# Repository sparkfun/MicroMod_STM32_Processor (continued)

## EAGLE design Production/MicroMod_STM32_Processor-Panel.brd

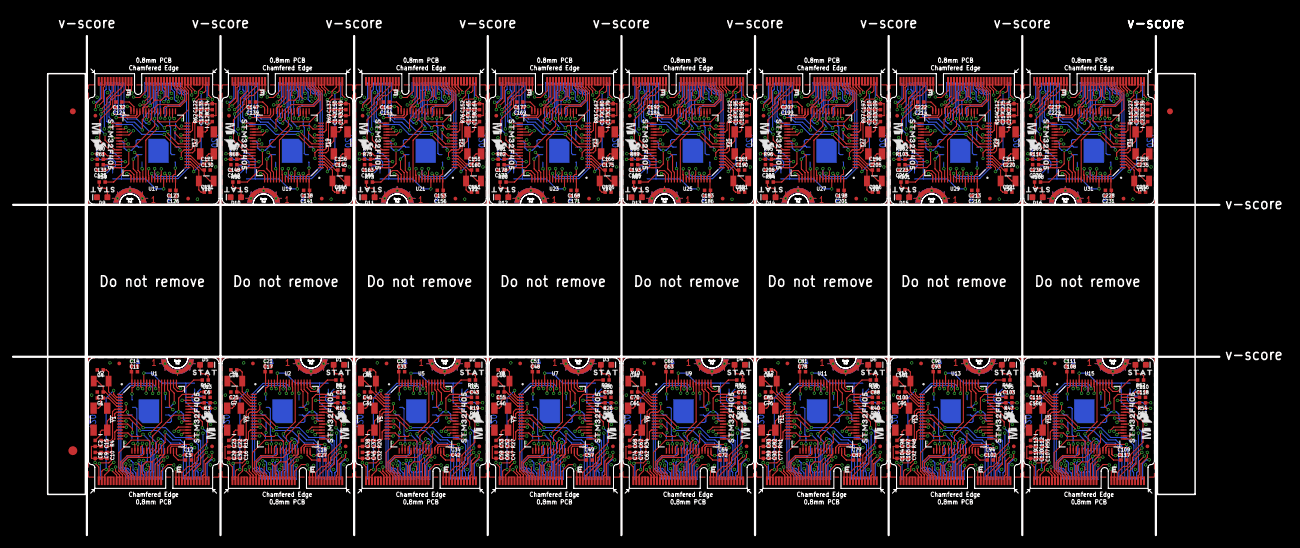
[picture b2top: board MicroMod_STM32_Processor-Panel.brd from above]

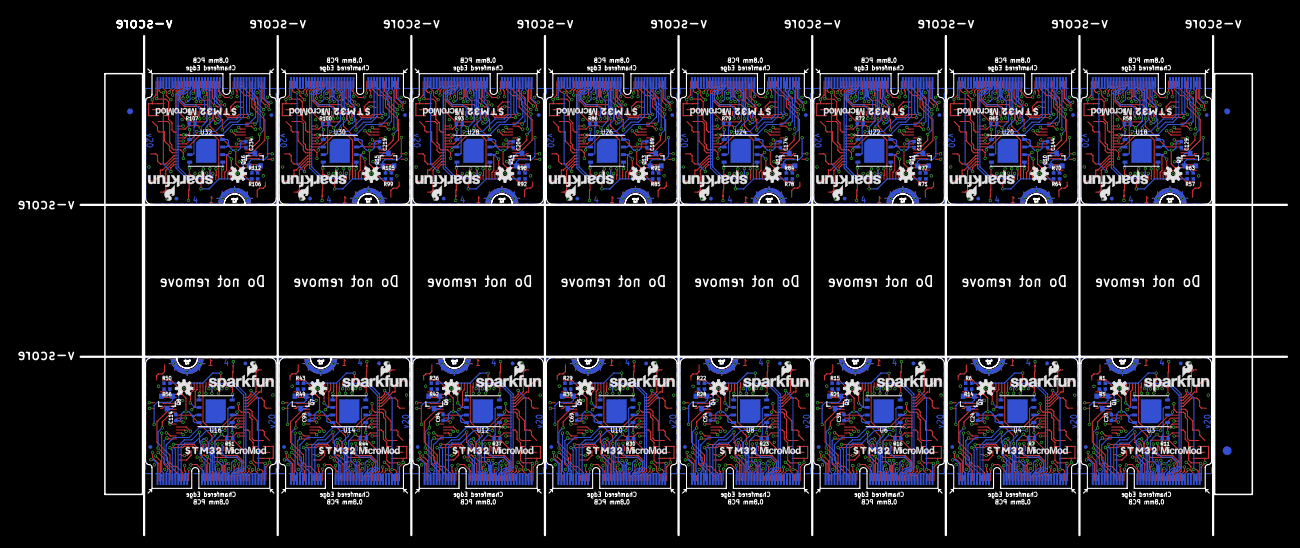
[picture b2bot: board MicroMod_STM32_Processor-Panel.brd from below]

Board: 4 copper layers, 203.2 x 84.1 mm, 662 parts (195 on the bottom side), 928 nets.

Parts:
C1, C2, C7, C23, C31, C38, C46, C53, C61, C68, C76, C83, C91, C98, C106, C113, C121, C128, C136, C143, C151, C158, C166, C173, C181, C188, C196, C203, C211, C218, C226, C233: 22pF; 0402-TIGHT
C3, C4, C25, C26, C40, C41, C55, C56, C70, C71, C85, C86, C100, C101, C115, C116, C130, C131, C145, C146, C160, C161, C175, C176, C190, C191, C205, C206, C220, C221, C235, C236: 15pF; 0402-TIGHT
C5, C6, C27, C28, C42, C43, C57, C58, C72, C73, C87, C88, C102, C103, C117, C118, C132, C133, C147, C148, C162, C163, C177, C178, C192, C193, C207, C208, C222, C223, C237, C238: 2.2uF; 0402-TIGHT
C8, C11, C12, C13, C14, C15, C17, C18, C19, C20, C21, C22, C24, C29, C33, C34, C35, C36, C37, C39, C44, C48, C49, C50, C51, C52, C54, C59, C63, C64, C65, C66, C67, C69, C74, C78, C79, C80, C81, C82, C84, C89, C93, C94, C95, C96, C97, C99, C104, C108, C109, C110, C111, C112, C114, C119, C123, C124, C125, C126, C127, C129, C134, C138, C139, C140, C141, C142, C144, C149, C153, C154, C155, C156, C157, C159, C164, C168, C169, C170, C171, C172, C174, C179, C183, C184, C185, C186, C187, C189, C194, C198, C199, C200, C201, C202, C204, C209, C213, C214, C215, C216, C217, C219, C224, C228, C229, C230, C231, C232, C234, C239: 0.1uF; 0402-TIGHT
C9, C30, C45, C60, C75, C90, C105, C120, C135, C150, C165, C180, C195, C210, C225, C240: 1.0uF; 0402-TIGHT
C10, C16, C32, C47, C62, C77, C92, C107, C122, C137, C152, C167, C182, C197, C212, C227: 4.7uF; 0402-TIGHT
D1, D2, D3, D4, D5, D6, D7, D8, D9, D10, D11, D12, D13, D14, D15, D16: BLUE; LED-0603
E$1, E$2, E$3, E$4: FIDUCIAL-1X2
E$5, E$6: FIDUCIAL-1.5X3
FD1, FD2, FD3, FD4, FD5, FD6, FD7, FD8, FD9, FD10, FD11, FD12, FD13, FD14, FD15, FD16, FD17, FD18, FD19, FD20, FD21, FD22, FD23, FD24, FD25, FD26, FD27, FD28, FD29, FD30, FD31, FD32, FD33, FD34, FD35, FD36, FD37, FD38, FD39, FD40, FD41, FD42, FD43, FD44, FD45, FD46, FD47, FD48, FD49, FD50, FD51, FD52, FD53, FD54, FD55, FD56, FD57, FD58, FD59, FD60, FD61, FD62, FD63, FD64: FIDUCIALUFIDUCIAL; FIDUCIAL-MICRO
J1, J2, J3, J4, J5, J6, J7, J8, J9, J10, J11, J12, J13, J14, J15, J16: MICROMOD-2222; M.2-CARD-E-22
LOGO1, LOGO2, LOGO5, LOGO7, LOGO9, LOGO11, LOGO13, LOGO15, LOGO17, LOGO19, LOGO21, LOGO23, LOGO25, LOGO27, LOGO29, LOGO31: OSHW-LOGOS; OSHW-LOGO-S
LOGO3, LOGO4, LOGO6, LOGO8, LOGO10, LOGO12, LOGO14, LOGO16, LOGO18, LOGO20, LOGO22, LOGO24, LOGO26, LOGO28, LOGO30, LOGO32: SFE_LOGO_NAME_FLAME.1_INCH; SFE_LOGO_NAME_FLAME_.1
Q1, Q2, Q3, Q4, Q5, Q6, Q7, Q8, Q9, Q10, Q11, Q12, Q13, Q14, Q15, Q16: SOT23-3
R1, R5, R6, R7, R11, R14, R15, R16, R21, R22, R23, R28, R29, R30, R35, R36, R37, R42, R43, R44, R49, R50, R51, R56, R57, R58, R63, R64, R65, R70, R71, R72, R77, R78, R79, R84, R85, R86, R91, R92, R93, R98, R99, R100, R105, R106, R107, R112: 100k; 0402-TIGHT
R2, R3, R9, R10, R18, R19, R25, R26, R32, R33, R39, R40, R46, R47, R53, R54, R60, R61, R67, R68, R74, R75, R81, R82, R88, R89, R95, R96, R102, R103, R109, R110: 22; 0402-TIGHT
R4, R13, R20, R27, R34, R41, R48, R55, R62, R69, R76, R83, R90, R97, R104, R111: 5.1k; 0402-TIGHT
R8, R12, R17, R24, R31, R38, R45, R52, R59, R66, R73, R80, R87, R94, R101, R108: 1k; 0402-TIGHT
U1, U2, U5, U7, U9, U11, U13, U15, U17, U19, U21, U23, U25, U27, U29, U31: STM32F405RGT6; TQFP64
U3, U4, U6, U8, U10, U12, U14, U16, U18, U20, U22, U24, U26, U28, U30, U32: W25QXX128MBIT-6X5; WSON-8-6X5
U$1, U$7, U$13, U$19, U$25, U$31, U$37, U$43, U$49, U$55, U$61, U$67, U$73, U$79, U$85, U$91: STAT0
U$2, U$8, U$14, U$20, U$26, U$32, U$38, U$44, U$50, U$56, U$62, U$68, U$74, U$80, U$86, U$92: STM320
U$3, U$9, U$15, U$21, U$27, U$33, U$39, U$45, U$51, U$57, U$63, U$69, U$75, U$81, U$87, U$93: MICROMOD_MI_LOGO_.35
U$4, U$10, U$16, U$22, U$28, U$34, U$40, U$46, U$52, U$58, U$64, U$70, U$76, U$82, U$88, U$94: STM32F4050
U$5, U$11, U$17, U$23, U$29, U$35, U$41, U$47, U$53, U$59, U$65, U$71, U$77, U$83, U$89, U$95: MICROMOD_LOGO_.3
U$6, U$12, U$18, U$24, U$30, U$36, U$42, U$48, U$54, U$60, U$66, U$72, U$78, U$84, U$90, U$96: SFE_LOGO_FLAME_.1
Y1, Y3, Y5, Y7, Y9, Y11, Y13, Y15, Y17, Y19, Y21, Y23, Y25, Y27, Y29, Y31: 12MHz; CRYSTAL-SMD-5X3.2-4PAD
Y2, Y4, Y6, Y8, Y10, Y12, Y14, Y16, Y18, Y20, Y22, Y24, Y26, Y28, Y30, Y32: 32.768kHz; CRYSTAL-SMD-3.2X1.5MM

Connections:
3.3V: C8.1, C9.1, C10.1, C11.1, C12.1, C13.1, C14.1, C20.1, J1.2, J1.74, Q1.2, R4.2, R5.2, R11.2, U1.13, U1.19, U1.32, U1.48, U1.64, U3.3, U3.7, U3.8
3.3V1: C16.1, C17.1, C18.1, C19.1, C21.1, C24.1, C29.1, C30.1, J2.2, J2.74, Q2.2, R7.2, R13.2, R14.2, U2.13, U2.19, U2.32, U2.48, U2.64, U4.3, U4.7, U4.8
3.3V2: C32.1, C33.1, C34.1, C35.1, C36.1, C39.1, C44.1, C45.1, J3.2, J3.74, Q3.2, R16.2, R20.2, R21.2, U5.13, U5.19, U5.32, U5.48, U5.64, U6.3, U6.7, U6.8
3.3V3: C47.1, C48.1, C49.1, C50.1, C51.1, C54.1, C59.1, C60.1, J4.2, J4.74, Q4.2, R23.2, R27.2, R28.2, U7.13, U7.19, U7.32, U7.48, U7.64, U8.3, U8.7, U8.8
3.3V4: C62.1, C63.1, C64.1, C65.1, C66.1, C69.1, C74.1, C75.1, J5.2, J5.74, Q5.2, R30.2, R34.2, R35.2, U9.13, U9.19, U9.32, U9.48, U9.64, U10.3, U10.7, U10.8
3.3V5: C77.1, C78.1, C79.1, C80.1, C81.1, C84.1, C89.1, C90.1, J6.2, J6.74, Q6.2, R37.2, R41.2, R42.2, U11.13, U11.19, U11.32, U11.48, U11.64, U12.3, U12.7, U12.8
3.3V6: C92.1, C93.1, C94.1, C95.1, C96.1, C99.1, C104.1, C105.1, J7.2, J7.74, Q7.2, R44.2, R48.2, R49.2, U13.13, U13.19, U13.32, U13.48, U13.64, U14.3, U14.7, U14.8
3.3V7: C107.1, C108.1, C109.1, C110.1, C111.1, C114.1, C119.1, C120.1, J8.2, J8.74, Q8.2, R51.2, R55.2, R56.2, U15.13, U15.19, U15.32, U15.48, U15.64, U16.3, U16.7, U16.8
3.3V8: C122.1, C123.1, C124.1, C125.1, C126.1, C129.1, C134.1, C135.1, J9.2, J9.74, Q9.2, R58.2, R62.2, R63.2, U17.13, U17.19, U17.32, U17.48, U17.64, U18.3, U18.7, U18.8
3.3V9: C137.1, C138.1, C139.1, C140.1, C141.1, C144.1, C149.1, C150.1, J10.2, J10.74, Q10.2, R65.2, R69.2, R70.2, U19.13, U19.19, U19.32, U19.48, U19.64, U20.3, U20.7, U20.8
3.3V10: C152.1, C153.1, C154.1, C155.1, C156.1, C159.1, C164.1, C165.1, J11.2, J11.74, Q11.2, R72.2, R76.2, R77.2, U21.13, U21.19, U21.32, U21.48, U21.64, U22.3, U22.7, U22.8
3.3V11: C167.1, C168.1, C169.1, C170.1, C171.1, C174.1, C179.1, C180.1, J12.2, J12.74, Q12.2, R79.2, R83.2, R84.2, U23.13, U23.19, U23.32, U23.48, U23.64, U24.3, U24.7, U24.8
3.3V12: C182.1, C183.1, C184.1, C185.1, C186.1, C189.1, C194.1, C195.1, J13.2, J13.74, Q13.2, R86.2, R90.2, R91.2, U25.13, U25.19, U25.32, U25.48, U25.64, U26.3, U26.7, U26.8
3.3V13: C197.1, C198.1, C199.1, C200.1, C201.1, C204.1, C209.1, C210.1, J14.2, J14.74, Q14.2, R93.2, R97.2, R98.2, U27.13, U27.19, U27.32, U27.48, U27.64, U28.3, U28.7, U28.8
3.3V14: C212.1, C213.1, C214.1, C215.1, C216.1, C219.1, C224.1, C225.1, J15.2, J15.74, Q15.2, R100.2, R104.2, R105.2, U29.13, U29.19, U29.32, U29.48, U29.64, U30.3, U30.7, U30.8
3.3V15: C227.1, C228.1, C229.1, C230.1, C231.1, C234.1, C239.1, C240.1, J16.2, J16.74, Q16.2, R107.2, R111.2, R112.2, U31.13, U31.19, U31.32, U31.48, U31.64, U32.3, U32.7, U32.8
!BOOT: J1.11, Q1.1, R5.1
!BOOT1: J2.11, Q2.1, R14.1
!BOOT2: J3.11, Q3.1, R21.1
!BOOT3: J4.11, Q4.1, R28.1
!BOOT4: J5.11, Q5.1, R35.1
!BOOT5: J6.11, Q6.1, R42.1
!BOOT6: J7.11, Q7.1, R49.1
!BOOT7: J8.11, Q8.1, R56.1
!BOOT8: J9.11, Q9.1, R63.1
!BOOT9: J10.11, Q10.1, R70.1
!BOOT10: J11.11, Q11.1, R77.1
!BOOT11: J12.11, Q12.1, R84.1
!BOOT12: J13.11, Q13.1, R91.1
!BOOT13: J14.11, Q14.1, R98.1
!BOOT14: J15.11, Q15.1, R105.1
!BOOT15: J16.11, Q16.1, R112.1
!CS: J1.55, U1.24
!CS1: J2.55, U2.24
!CS2: J3.55, U5.24
!CS3: J4.55, U7.24
!CS4: J5.55, U9.24
!CS5: J6.55, U11.24
!CS6: J7.55, U13.24
!CS7: J8.55, U15.24
!CS8: J9.55, U17.24
!CS9: J10.55, U19.24
!CS10: J11.55, U21.24
!CS11: J12.55, U23.24
!CS12: J13.55, U25.24
!CS13: J14.55, U27.24
!CS14: J15.55, U29.24
!CS15: J16.55, U31.24
!INT: J1.16, U1.27
!INT1: J2.16, U2.27
!INT2: J3.16, U5.27
!INT3: J4.16, U7.27
!INT4: J5.16, U9.27
!INT5: J6.16, U11.27
!INT6: J7.16, U13.27
!INT7: J8.16, U15.27
!INT8: J9.16, U17.27
!INT9: J10.16, U19.27
!INT10: J11.16, U21.27
!INT11: J12.16, U23.27
!INT12: J13.16, U25.27
!INT13: J14.16, U27.27
!INT14: J15.16, U29.27
!INT15: J16.16, U31.27
!RESET: C15.1, J1.6, R4.1, U1.7
!RESET1: C22.1, J2.6, R13.1, U2.7
!RESET2: C37.1, J3.6, R20.1, U5.7
!RESET3: C52.1, J4.6, R27.1, U7.7
!RESET4: C67.1, J5.6, R34.1, U9.7
!RESET5: C82.1, J6.6, R41.1, U11.7
!RESET6: C97.1, J7.6, R48.1, U13.7
!RESET7: C112.1, J8.6, R55.1, U15.7
!RESET8: C127.1, J9.6, R62.1, U17.7
!RESET9: C142.1, J10.6, R69.1, U19.7
!RESET10: C157.1, J11.6, R76.1, U21.7
!RESET11: C172.1, J12.6, R83.1, U23.7
!RESET12: C187.1, J13.6, R90.1, U25.7
!RESET13: C202.1, J14.6, R97.1, U27.7
!RESET14: C217.1, J15.6, R104.1, U29.7
!RESET15: C232.1, J16.6, R111.1, U31.7
A0: J1.34, U1.25
A1: J1.38, U1.26
A2: J2.34, U2.25
A3: J2.38, U2.26
A4: J3.34, U5.25
A5: J3.38, U5.26
A6: J4.34, U7.25
A7: J4.38, U7.26
A8: J5.34, U9.25
A9: J5.38, U9.26
A10: J6.34, U11.25
A11: J6.38, U11.26
A12: J7.34, U13.25
A13: J7.38, U13.26
A14: J8.34, U15.25
A15: J8.38, U15.26
A16: J9.34, U17.25
A17: J9.38, U17.26
A18: J10.34, U19.25
A19: J10.38, U19.26
A20: J11.34, U21.25
A21: J11.38, U21.26
A22: J12.34, U23.25
A23: J12.38, U23.26
A24: J13.34, U25.25
A25: J13.38, U25.26
A26: J14.34, U27.25
A27: J14.38, U27.26
A28: J15.34, U29.25
A29: J15.38, U29.26
A30: J16.34, U31.25
A31: J16.38, U31.26
AUD_BCLK: J1.50, U1.55
AUD_BCLK1: J2.50, U2.55
AUD_BCLK2: J3.50, U5.55
AUD_BCLK3: J4.50, U7.55
AUD_BCLK4: J5.50, U9.55
AUD_BCLK5: J6.50, U11.55
AUD_BCLK6: J7.50, U13.55
AUD_BCLK7: J8.50, U15.55
AUD_BCLK8: J9.50, U17.55
AUD_BCLK9: J10.50, U19.55
AUD_BCLK10: J11.50, U21.55
AUD_BCLK11: J12.50, U23.55
AUD_BCLK12: J13.50, U25.55
AUD_BCLK13: J14.50, U27.55
AUD_BCLK14: J15.50, U29.55
AUD_BCLK15: J16.50, U31.55
AUD_IN: J1.54, U1.57
AUD_IN1: J2.54, U2.57
AUD_IN2: J3.54, U5.57
AUD_IN3: J4.54, U7.57
AUD_IN4: J5.54, U9.57
AUD_IN5: J6.54, U11.57
AUD_IN6: J7.54, U13.57
AUD_IN7: J8.54, U15.57
AUD_IN8: J9.54, U17.57
AUD_IN9: J10.54, U19.57
AUD_IN10: J11.54, U21.57
AUD_IN11: J12.54, U23.57
AUD_IN12: J13.54, U25.57
AUD_IN13: J14.54, U27.57
AUD_IN14: J15.54, U29.57
AUD_IN15: J16.54, U31.57
AUD_LRCLK: J1.52, U1.20
AUD_LRCLK1: J2.52, U2.20
AUD_LRCLK2: J3.52, U5.20
AUD_LRCLK3: J4.52, U7.20
AUD_LRCLK4: J5.52, U9.20
AUD_LRCLK5: J6.52, U11.20
AUD_LRCLK6: J7.52, U13.20
AUD_LRCLK7: J8.52, U15.20
AUD_LRCLK8: J9.52, U17.20
AUD_LRCLK9: J10.52, U19.20
AUD_LRCLK10: J11.52, U21.20
AUD_LRCLK11: J12.52, U23.20
AUD_LRCLK12: J13.52, U25.20
AUD_LRCLK13: J14.52, U27.20
AUD_LRCLK14: J15.52, U29.20
AUD_LRCLK15: J16.52, U31.20
AUD_OUT: J1.56, U1.56
AUD_OUT1: J2.56, U2.56
AUD_OUT2: J3.56, U5.56
AUD_OUT3: J4.56, U7.56
AUD_OUT4: J5.56, U9.56
AUD_OUT5: J6.56, U11.56
AUD_OUT6: J7.56, U13.56
AUD_OUT7: J8.56, U15.56
AUD_OUT8: J9.56, U17.56
AUD_OUT9: J10.56, U19.56
AUD_OUT10: J11.56, U21.56
AUD_OUT11: J12.56, U23.56
AUD_OUT12: J13.56, U25.56
AUD_OUT13: J14.56, U27.56
AUD_OUT14: J15.56, U29.56
AUD_OUT15: J16.56, U31.56
BATT_VIN: J1.49, U1.15
BATT_VIN1: J2.49, U2.15
BATT_VIN2: J3.49, U5.15
BATT_VIN3: J4.49, U7.15
BATT_VIN4: J5.49, U9.15
BATT_VIN5: J6.49, U11.15
BATT_VIN6: J7.49, U13.15
BATT_VIN7: J8.49, U15.15
BATT_VIN8: J9.49, U17.15
BATT_VIN9: J10.49, U19.15
BATT_VIN10: J11.49, U21.15
BATT_VIN11: J12.49, U23.15
BATT_VIN12: J13.49, U25.15
BATT_VIN13: J14.49, U27.15
BATT_VIN14: J15.49, U29.15
BATT_VIN15: J16.49, U31.15
BOOT0: Q1.3, R1.2, U1.60
BOOT1: Q2.3, R6.2, U2.60
BOOT2: Q3.3, R15.2, U5.60
BOOT3: Q4.3, R22.2, U7.60
BOOT4: Q5.3, R29.2, U9.60
BOOT5: Q6.3, R36.2, U11.60
BOOT6: Q7.3, R43.2, U13.60
BOOT7: Q8.3, R50.2, U15.60
BOOT8: Q9.3, R57.2, U17.60
BOOT9: Q10.3, R64.2, U19.60
BOOT10: Q11.3, R71.2, U21.60
BOOT11: Q12.3, R78.2, U23.60
BOOT12: Q13.3, R85.2, U25.60
BOOT13: Q14.3, R92.2, U27.60
BOOT14: Q15.3, R99.2, U29.60
BOOT15: Q16.3, R106.2, U31.60
CAN_RX: J1.41, U1.61
CAN_RX1: J2.41, U2.61
CAN_RX2: J3.41, U5.61
CAN_RX3: J4.41, U7.61
CAN_RX4: J5.41, U9.61
CAN_RX5: J6.41, U11.61
CAN_RX6: J7.41, U13.61
CAN_RX7: J8.41, U15.61
CAN_RX8: J9.41, U17.61
CAN_RX9: J10.41, U19.61
CAN_RX10: J11.41, U21.61
CAN_RX11: J12.41, U23.61
CAN_RX12: J13.41, U25.61
CAN_RX13: J14.41, U27.61
CAN_RX14: J15.41, U29.61
CAN_RX15: J16.41, U31.61
CAN_TX: J1.43, U1.62
CAN_TX1: J2.43, U2.62
CAN_TX2: J3.43, U5.62
CAN_TX3: J4.43, U7.62
CAN_TX4: J5.43, U9.62
CAN_TX5: J6.43, U11.62
CAN_TX6: J7.43, U13.62
CAN_TX7: J8.43, U15.62
CAN_TX8: J9.43, U17.62
CAN_TX9: J10.43, U19.62
CAN_TX10: J11.43, U21.62
CAN_TX11: J12.43, U23.62
CAN_TX12: J13.43, U25.62
CAN_TX13: J14.43, U27.62
CAN_TX14: J15.43, U29.62
CAN_TX15: J16.43, U31.62
D0: J1.10, U1.8
D1: J1.18, U1.9
D2: J2.10, U2.8
D3: J2.18, U2.9
D4: J3.10, U5.8
D5: J3.18, U5.9
D6: J4.10, U7.8
D7: J4.18, U7.9
D8: J5.10, U9.8
D9: J5.18, U9.9
D10: J6.10, U11.8
D11: J6.18, U11.9
D12: J7.10, U13.8
D13: J7.18, U13.9
D14: J8.10, U15.8
D15: J8.18, U15.9
D16: J9.10, U17.8
D17: J9.18, U17.9
D18: J10.10, U19.8
D19: J10.18, U19.9
D20: J11.10, U21.8
D21: J11.18, U21.9
D22: J12.10, U23.8
D23: J12.18, U23.9
D24: J13.10, U25.8
D25: J13.18, U25.9
D26: J14.10, U27.8
D27: J14.18, U27.9
D28: J15.10, U29.8
D29: J15.18, U29.9
D30: J16.10, U31.8
D31: J16.18, U31.9
D+: J1.3, R3.1
D+1: J2.3, R10.1
D+2: J3.3, R19.1
D+3: J4.3, R26.1
D+4: J5.3, R33.1
D+5: J6.3, R40.1
D+6: J7.3, R47.1
D+7: J8.3, R54.1
D+8: J9.3, R61.1
D+9: J10.3, R68.1
D+10: J11.3, R75.1
D+11: J12.3, R82.1
D+12: J13.3, R89.1
D+13: J14.3, R96.1
D+14: J15.3, R103.1
D+15: J16.3, R110.1
D-: J1.5, R2.1
D-1: J2.5, R9.1
D-2: J3.5, R18.1
D-3: J4.5, R25.1
D-4: J5.5, R32.1
D-5: J6.5, R39.1
D-6: J7.5, R46.1
D-7: J8.5, R53.1
D-8: J9.5, R60.1
D-9: J10.5, R67.1
D-10: J11.5, R74.1
D-11: J12.5, R81.1
D-12: J13.5, R88.1
D-13: J14.5, R95.1
D-14: J15.5, R102.1
D-15: J16.5, R109.1
FLASH_!CS: R11.1, U1.11, U3.1
FLASH_!CS1: R7.1, U2.11, U4.1
FLASH_!CS2: R16.1, U5.11, U6.1
FLASH_!CS3: R23.1, U7.11, U8.1
FLASH_!CS4: R30.1, U9.11, U10.1
FLASH_!CS5: R37.1, U11.11, U12.1
FLASH_!CS6: R44.1, U13.11, U14.1
FLASH_!CS7: R51.1, U15.11, U16.1
FLASH_!CS8: R58.1, U17.11, U18.1
FLASH_!CS9: R65.1, U19.11, U20.1
FLASH_!CS10: R72.1, U21.11, U22.1
FLASH_!CS11: R79.1, U23.11, U24.1
FLASH_!CS12: R86.1, U25.11, U26.1
FLASH_!CS13: R93.1, U27.11, U28.1
FLASH_!CS14: R100.1, U29.11, U30.1
FLASH_!CS15: R107.1, U31.11, U32.1
FLASH_SCK: U1.51, U3.6
FLASH_SCK1: U2.51, U4.6
FLASH_SCK2: U5.51, U6.6
FLASH_SCK3: U7.51, U8.6
FLASH_SCK4: U9.51, U10.6
FLASH_SCK5: U11.51, U12.6
FLASH_SCK6: U13.51, U14.6
FLASH_SCK7: U15.51, U16.6
FLASH_SCK8: U17.51, U18.6
FLASH_SCK9: U19.51, U20.6
FLASH_SCK10: U21.51, U22.6
FLASH_SCK11: U23.51, U24.6
FLASH_SCK12: U25.51, U26.6
FLASH_SCK13: U27.51, U28.6
FLASH_SCK14: U29.51, U30.6
FLASH_SCK15: U31.51, U32.6
FLASH_SDI: U1.53, U3.5
FLASH_SDI1: U2.53, U4.5
FLASH_SDI2: U5.53, U6.5
FLASH_SDI3: U7.53, U8.5
FLASH_SDI4: U9.53, U10.5
FLASH_SDI5: U11.53, U12.5
FLASH_SDI6: U13.53, U14.5
FLASH_SDI7: U15.53, U16.5
FLASH_SDI8: U17.53, U18.5
FLASH_SDI9: U19.53, U20.5
FLASH_SDI10: U21.53, U22.5
FLASH_SDI11: U23.53, U24.5
FLASH_SDI12: U25.53, U26.5
FLASH_SDI13: U27.53, U28.5
FLASH_SDI14: U29.53, U30.5
FLASH_SDI15: U31.53, U32.5
FLASH_SDO: U1.52, U3.2
FLASH_SDO1: U2.52, U4.2
FLASH_SDO2: U5.52, U6.2
FLASH_SDO3: U7.52, U8.2
FLASH_SDO4: U9.52, U10.2
FLASH_SDO5: U11.52, U12.2
FLASH_SDO6: U13.52, U14.2
FLASH_SDO7: U15.52, U16.2
FLASH_SDO8: U17.52, U18.2
FLASH_SDO9: U19.52, U20.2
FLASH_SDO10: U21.52, U22.2
FLASH_SDO11: U23.52, U24.2
FLASH_SDO12: U25.52, U26.2
FLASH_SDO13: U27.52, U28.2
FLASH_SDO14: U29.52, U30.2
FLASH_SDO15: U31.52, U32.2
G0: J1.40, U1.54
G1: J1.42, U1.41
G2: J1.44, U1.14
G3: J1.46, U1.39
G4: J1.48, U1.40
G5: J1.73, U1.2
G6: J1.71, U1.10
G7: J2.73, U2.2
G8: J2.71, U2.10
G9: J2.46, U2.39
G10: J2.48, U2.40
G11: J2.40, U2.54
G12: J2.42, U2.41
G13: J2.44, U2.14
G14: J3.73, U5.2
G15: J3.71, U5.10
G16: J3.46, U5.39
G17: J3.48, U5.40
G18: J3.40, U5.54
G19: J3.42, U5.41
G20: J3.44, U5.14
G21: J4.73, U7.2
G22: J4.71, U7.10
G23: J4.46, U7.39
G24: J4.48, U7.40
G25: J4.40, U7.54
G26: J4.42, U7.41
G27: J4.44, U7.14
G28: J5.73, U9.2
G29: J5.71, U9.10
G30: J5.46, U9.39
G31: J5.48, U9.40
G32: J5.40, U9.54
G33: J5.42, U9.41
G34: J5.44, U9.14
G35: J6.73, U11.2
G36: J6.71, U11.10
G37: J6.46, U11.39
G38: J6.48, U11.40
G39: J6.40, U11.54
G40: J6.42, U11.41
G41: J6.44, U11.14
G42: J7.73, U13.2
G43: J7.71, U13.10
G44: J7.46, U13.39
G45: J7.48, U13.40
G46: J7.40, U13.54
G47: J7.42, U13.41
G48: J7.44, U13.14
G49: J8.73, U15.2
G50: J8.71, U15.10
G51: J8.46, U15.39
G52: J8.48, U15.40
G53: J8.40, U15.54
G54: J8.42, U15.41
G55: J8.44, U15.14
G56: J9.73, U17.2
G57: J9.71, U17.10
G58: J9.46, U17.39
G59: J9.48, U17.40
G60: J9.40, U17.54
G61: J9.42, U17.41
G62: J9.44, U17.14
G63: J10.73, U19.2
G64: J10.71, U19.10
G65: J10.46, U19.39
G66: J10.48, U19.40
G67: J10.40, U19.54
G68: J10.42, U19.41
G69: J10.44, U19.14
G70: J11.73, U21.2
G71: J11.71, U21.10
G72: J11.46, U21.39
G73: J11.48, U21.40
G74: J11.40, U21.54
G75: J11.42, U21.41
G76: J11.44, U21.14
G77: J12.73, U23.2
G78: J12.71, U23.10
G79: J12.46, U23.39
G80: J12.48, U23.40
G81: J12.40, U23.54
G82: J12.42, U23.41
G83: J12.44, U23.14
G84: J13.73, U25.2
G85: J13.71, U25.10
G86: J13.46, U25.39
G87: J13.48, U25.40
G88: J13.40, U25.54
G89: J13.42, U25.41
G90: J13.44, U25.14
G91: J14.73, U27.2
G92: J14.71, U27.10
G93: J14.46, U27.39
G94: J14.48, U27.40
G95: J14.40, U27.54
G96: J14.42, U27.41
G97: J14.44, U27.14
G98: J15.73, U29.2
G99: J15.71, U29.10
G100: J15.46, U29.39
G101: J15.48, U29.40
G102: J15.40, U29.54
G103: J15.42, U29.41
G104: J15.44, U29.14
G105: J16.73, U31.2
G106: J16.71, U31.10
G107: J16.46, U31.39
G108: J16.48, U31.40
G109: J16.40, U31.54
G110: J16.42, U31.41
G111: J16.44, U31.14
GND: C1.2, C2.2, C3.2, C4.2, C5.2, C6.2, C8.2, C9.2, C10.2, C11.2, C12.2, C13.2, C14.2, C15.2, C20.2, D5.C, J1.1, J1.7, J1.33, J1.36, J1.39, J1.45, J1.75, J1.GND1, J1.GND2, J1.GND3, R1.1, U1.12, U1.16, U1.17, U1.18, U1.28, U1.63, U3.4
GND1: C7.2, C16.2, C17.2, C18.2, C19.2, C21.2, C22.2, C23.2, C24.2, C25.2, C26.2, C27.2, C28.2, C29.2, C30.2, D1.C, J2.1, J2.7, J2.33, J2.36, J2.39, J2.45, J2.75, J2.GND1, J2.GND2, J2.GND3, R6.1, U2.12, U2.16, U2.17, U2.18, U2.28, U2.63, U4.4
GND2: C31.2, C32.2, C33.2, C34.2, C35.2, C36.2, C37.2, C38.2, C39.2, C40.2, C41.2, C42.2, C43.2, C44.2, C45.2, D2.C, J3.1, J3.7, J3.33, J3.36, J3.39, J3.45, J3.75, J3.GND1, J3.GND2, J3.GND3, R15.1, U5.12, U5.16, U5.17, U5.18, U5.28, U5.63, U6.4
GND3: C46.2, C47.2, C48.2, C49.2, C50.2, C51.2, C52.2, C53.2, C54.2, C55.2, C56.2, C57.2, C58.2, C59.2, C60.2, D3.C, J4.1, J4.7, J4.33, J4.36, J4.39, J4.45, J4.75, J4.GND1, J4.GND2, J4.GND3, R22.1, U7.12, U7.16, U7.17, U7.18, U7.28, U7.63, U8.4
GND4: C61.2, C62.2, C63.2, C64.2, C65.2, C66.2, C67.2, C68.2, C69.2, C70.2, C71.2, C72.2, C73.2, C74.2, C75.2, D4.C, J5.1, J5.7, J5.33, J5.36, J5.39, J5.45, J5.75, J5.GND1, J5.GND2, J5.GND3, R29.1, U9.12, U9.16, U9.17, U9.18, U9.28, U9.63, U10.4
GND5: C76.2, C77.2, C78.2, C79.2, C80.2, C81.2, C82.2, C83.2, C84.2, C85.2, C86.2, C87.2, C88.2, C89.2, C90.2, D6.C, J6.1, J6.7, J6.33, J6.36, J6.39, J6.45, J6.75, J6.GND1, J6.GND2, J6.GND3, R36.1, U11.12, U11.16, U11.17, U11.18, U11.28, U11.63, U12.4
GND6: C91.2, C92.2, C93.2, C94.2, C95.2, C96.2, C97.2, C98.2, C99.2, C100.2, C101.2, C102.2, C103.2, C104.2, C105.2, D7.C, J7.1, J7.7, J7.33, J7.36, J7.39, J7.45, J7.75, J7.GND1, J7.GND2, J7.GND3, R43.1, U13.12, U13.16, U13.17, U13.18, U13.28, U13.63, U14.4
GND7: C106.2, C107.2, C108.2, C109.2, C110.2, C111.2, C112.2, C113.2, C114.2, C115.2, C116.2, C117.2, C118.2, C119.2, C120.2, D8.C, J8.1, J8.7, J8.33, J8.36, J8.39, J8.45, J8.75, J8.GND1, J8.GND2, J8.GND3, R50.1, U15.12, U15.16, U15.17, U15.18, U15.28, U15.63, U16.4
GND8: C121.2, C122.2, C123.2, C124.2, C125.2, C126.2, C127.2, C128.2, C129.2, C130.2, C131.2, C132.2, C133.2, C134.2, C135.2, D9.C, J9.1, J9.7, J9.33, J9.36, J9.39, J9.45, J9.75, J9.GND1, J9.GND2, J9.GND3, R57.1, U17.12, U17.16, U17.17, U17.18, U17.28, U17.63, U18.4
GND9: C136.2, C137.2, C138.2, C139.2, C140.2, C141.2, C142.2, C143.2, C144.2, C145.2, C146.2, C147.2, C148.2, C149.2, C150.2, D10.C, J10.1, J10.7, J10.33, J10.36, J10.39, J10.45, J10.75, J10.GND1, J10.GND2, J10.GND3, R64.1, U19.12, U19.16, U19.17, U19.18, U19.28, U19.63, U20.4
GND10: C151.2, C152.2, C153.2, C154.2, C155.2, C156.2, C157.2, C158.2, C159.2, C160.2, C161.2, C162.2, C163.2, C164.2, C165.2, D11.C, J11.1, J11.7, J11.33, J11.36, J11.39, J11.45, J11.75, J11.GND1, J11.GND2, J11.GND3, R71.1, U21.12, U21.16, U21.17, U21.18, U21.28, U21.63, U22.4
GND11: C166.2, C167.2, C168.2, C169.2, C170.2, C171.2, C172.2, C173.2, C174.2, C175.2, C176.2, C177.2, C178.2, C179.2, C180.2, D12.C, J12.1, J12.7, J12.33, J12.36, J12.39, J12.45, J12.75, J12.GND1, J12.GND2, J12.GND3, R78.1, U23.12, U23.16, U23.17, U23.18, U23.28, U23.63, U24.4
GND12: C181.2, C182.2, C183.2, C184.2, C185.2, C186.2, C187.2, C188.2, C189.2, C190.2, C191.2, C192.2, C193.2, C194.2, C195.2, D13.C, J13.1, J13.7, J13.33, J13.36, J13.39, J13.45, J13.75, J13.GND1, J13.GND2, J13.GND3, R85.1, U25.12, U25.16, U25.17, U25.18, U25.28, U25.63, U26.4
GND13: C196.2, C197.2, C198.2, C199.2, C200.2, C201.2, C202.2, C203.2, C204.2, C205.2, C206.2, C207.2, C208.2, C209.2, C210.2, D14.C, J14.1, J14.7, J14.33, J14.36, J14.39, J14.45, J14.75, J14.GND1, J14.GND2, J14.GND3, R92.1, U27.12, U27.16, U27.17, U27.18, U27.28, U27.63, U28.4
GND14: C211.2, C212.2, C213.2, C214.2, C215.2, C216.2, C217.2, C218.2, C219.2, C220.2, C221.2, C222.2, C223.2, C224.2, C225.2, D15.C, J15.1, J15.7, J15.33, J15.36, J15.39, J15.45, J15.75, J15.GND1, J15.GND2, J15.GND3, R99.1, U29.12, U29.16, U29.17, U29.18, U29.28, U29.63, U30.4
GND15: C226.2, C227.2, C228.2, C229.2, C230.2, C231.2, C232.2, C233.2, C234.2, C235.2, C236.2, C237.2, C238.2, C239.2, C240.2, D16.C, J16.1, J16.7, J16.33, J16.36, J16.39, J16.45, J16.75, J16.GND1, J16.GND2, J16.GND3, R106.1, U31.12, U31.16, U31.17, U31.18, U31.28, U31.63, U32.4
HOST_D+: J1.35, U1.36
HOST_D+1: J2.35, U2.36
HOST_D+2: J3.35, U5.36
HOST_D+3: J4.35, U7.36
HOST_D+4: J5.35, U9.36
HOST_D+5: J6.35, U11.36
HOST_D+6: J7.35, U13.36
HOST_D+7: J8.35, U15.36
HOST_D+8: J9.35, U17.36
HOST_D+9: J10.35, U19.36
HOST_D+10: J11.35, U21.36
HOST_D+11: J12.35, U23.36
HOST_D+12: J13.35, U25.36
HOST_D+13: J14.35, U27.36
HOST_D+14: J15.35, U29.36
HOST_D+15: J16.35, U31.36
HOST_D-: J1.37, U1.35
HOST_D-1: J2.37, U2.35
HOST_D-2: J3.37, U5.35
HOST_D-3: J4.37, U7.35
HOST_D-4: J5.37, U9.35
HOST_D-5: J6.37, U11.35
HOST_D-6: J7.37, U13.35
HOST_D-7: J8.37, U15.35
HOST_D-8: J9.37, U17.35
HOST_D-9: J10.37, U19.35
HOST_D-10: J11.37, U21.35
HOST_D-11: J12.37, U23.35
HOST_D-12: J13.37, U25.35
HOST_D-13: J14.37, U27.35
HOST_D-14: J15.37, U29.35
HOST_D-15: J16.37, U31.35
HOST_ID: J1.8, U1.33
HOST_ID1: J2.8, U2.33
HOST_ID2: J3.8, U5.33
HOST_ID3: J4.8, U7.33
HOST_ID4: J5.8, U9.33
HOST_ID5: J6.8, U11.33
HOST_ID6: J7.8, U13.33
HOST_ID7: J8.8, U15.33
HOST_ID8: J9.8, U17.33
HOST_ID9: J10.8, U19.33
HOST_ID10: J11.8, U21.33
HOST_ID11: J12.8, U23.33
HOST_ID12: J13.8, U25.33
HOST_ID13: J14.8, U27.33
HOST_ID14: J15.8, U29.33
HOST_ID15: J16.8, U31.33
HOST_VBUS: J1.63, U1.34
HOST_VBUS1: J2.63, U2.34
HOST_VBUS2: J3.63, U5.34
HOST_VBUS3: J4.63, U7.34
HOST_VBUS4: J5.63, U9.34
HOST_VBUS5: J6.63, U11.34
HOST_VBUS6: J7.63, U13.34
HOST_VBUS7: J8.63, U15.34
HOST_VBUS8: J9.63, U17.34
HOST_VBUS9: J10.63, U19.34
HOST_VBUS10: J11.63, U21.34
HOST_VBUS11: J12.63, U23.34
HOST_VBUS12: J13.63, U25.34
HOST_VBUS13: J14.63, U27.34
HOST_VBUS14: J15.63, U29.34
HOST_VBUS15: J16.63, U31.34
unnamed: D5.A, R12.1
unnamed: R2.2, U1.44
unnamed: R3.2, U1.45
unnamed: C26.1, U2.3, Y4.P$2
unnamed: C4.1, U1.3, Y2.P$2
unnamed: C3.1, U1.4, Y2.P$1
unnamed: C2.1, U1.6, Y1.3
unnamed: C1.1, U1.5, Y1.1
unnamed: C25.1, U2.4, Y4.P$1
unnamed: C23.1, U2.6, Y3.3
unnamed: C7.1, U2.5, Y3.1
unnamed: C28.1, U2.47
unnamed: C27.1, U2.31
unnamed: D1.A, R8.1
unnamed: R9.2, U2.44
unnamed: R10.2, U2.45
unnamed: C41.1, U5.3, Y6.P$2
unnamed: C40.1, U5.4, Y6.P$1
unnamed: C38.1, U5.6, Y5.3
unnamed: C31.1, U5.5, Y5.1
unnamed: C43.1, U5.47
unnamed: C42.1, U5.31
unnamed: D2.A, R17.1
unnamed: R18.2, U5.44
unnamed: R19.2, U5.45
unnamed: C56.1, U7.3, Y8.P$2
unnamed: C55.1, U7.4, Y8.P$1
unnamed: C53.1, U7.6, Y7.3
unnamed: C46.1, U7.5, Y7.1
unnamed: C58.1, U7.47
unnamed: C57.1, U7.31
unnamed: D3.A, R24.1
unnamed: R25.2, U7.44
unnamed: R26.2, U7.45
unnamed: C71.1, U9.3, Y10.P$2
unnamed: C70.1, U9.4, Y10.P$1
unnamed: C68.1, U9.6, Y9.3
unnamed: C61.1, U9.5, Y9.1
unnamed: C73.1, U9.47
unnamed: C72.1, U9.31
unnamed: D4.A, R31.1
unnamed: R32.2, U9.44
unnamed: R33.2, U9.45
unnamed: C86.1, U11.3, Y12.P$2
unnamed: C6.1, U1.47
unnamed: C5.1, U1.31
unnamed: C85.1, U11.4, Y12.P$1
unnamed: C83.1, U11.6, Y11.3
unnamed: C76.1, U11.5, Y11.1
unnamed: C88.1, U11.47
unnamed: C87.1, U11.31
unnamed: D6.A, R38.1
unnamed: R39.2, U11.44
unnamed: R40.2, U11.45
unnamed: C101.1, U13.3, Y14.P$2
unnamed: C100.1, U13.4, Y14.P$1
unnamed: C98.1, U13.6, Y13.3
unnamed: C91.1, U13.5, Y13.1
unnamed: C103.1, U13.47
unnamed: C102.1, U13.31
unnamed: D7.A, R45.1
unnamed: R46.2, U13.44
unnamed: R47.2, U13.45
unnamed: C116.1, U15.3, Y16.P$2
unnamed: C115.1, U15.4, Y16.P$1
unnamed: C113.1, U15.6, Y15.3
unnamed: C106.1, U15.5, Y15.1
unnamed: C118.1, U15.47
unnamed: C117.1, U15.31
unnamed: D8.A, R52.1
unnamed: R53.2, U15.44
unnamed: R54.2, U15.45
unnamed: C131.1, U17.3, Y18.P$2
unnamed: C130.1, U17.4, Y18.P$1
unnamed: C128.1, U17.6, Y17.3
unnamed: C121.1, U17.5, Y17.1
unnamed: C133.1, U17.47
unnamed: C132.1, U17.31
unnamed: D9.A, R59.1
unnamed: R60.2, U17.44
unnamed: R61.2, U17.45
unnamed: C146.1, U19.3, Y20.P$2
unnamed: C145.1, U19.4, Y20.P$1
unnamed: C143.1, U19.6, Y19.3
unnamed: C136.1, U19.5, Y19.1
unnamed: C148.1, U19.47
unnamed: C147.1, U19.31
unnamed: D10.A, R66.1
unnamed: R67.2, U19.44
unnamed: R68.2, U19.45
unnamed: C161.1, U21.3, Y22.P$2
unnamed: C160.1, U21.4, Y22.P$1
unnamed: C158.1, U21.6, Y21.3
unnamed: C151.1, U21.5, Y21.1
unnamed: C163.1, U21.47
unnamed: C162.1, U21.31
unnamed: D11.A, R73.1
unnamed: R74.2, U21.44
unnamed: R75.2, U21.45
unnamed: C176.1, U23.3, Y24.P$2
unnamed: C175.1, U23.4, Y24.P$1
unnamed: C173.1, U23.6, Y23.3
unnamed: C166.1, U23.5, Y23.1
unnamed: C178.1, U23.47
unnamed: C177.1, U23.31
unnamed: D12.A, R80.1
unnamed: R81.2, U23.44
unnamed: R82.2, U23.45
unnamed: C191.1, U25.3, Y26.P$2
unnamed: C190.1, U25.4, Y26.P$1
unnamed: C188.1, U25.6, Y25.3
unnamed: C181.1, U25.5, Y25.1
unnamed: C193.1, U25.47
unnamed: C192.1, U25.31
unnamed: D13.A, R87.1
unnamed: R88.2, U25.44
unnamed: R89.2, U25.45
unnamed: C206.1, U27.3, Y28.P$2
unnamed: C205.1, U27.4, Y28.P$1
unnamed: C203.1, U27.6, Y27.3
unnamed: C196.1, U27.5, Y27.1
unnamed: C208.1, U27.47
unnamed: C207.1, U27.31
unnamed: D14.A, R94.1
unnamed: R95.2, U27.44
unnamed: R96.2, U27.45
unnamed: C221.1, U29.3, Y30.P$2
unnamed: C220.1, U29.4, Y30.P$1
unnamed: C218.1, U29.6, Y29.3
unnamed: C211.1, U29.5, Y29.1
unnamed: C223.1, U29.47
unnamed: C222.1, U29.31
unnamed: D15.A, R101.1
unnamed: R102.2, U29.44
unnamed: R103.2, U29.45
unnamed: C236.1, U31.3, Y32.P$2
unnamed: C235.1, U31.4, Y32.P$1
unnamed: C233.1, U31.6, Y31.3
unnamed: C226.1, U31.5, Y31.1
unnamed: C238.1, U31.47
unnamed: C237.1, U31.31
unnamed: D16.A, R108.1
unnamed: R109.2, U31.44
unnamed: R110.2, U31.45
PICO: J1.59, U1.23
PICO1: J2.59, U2.23
PICO2: J3.59, U5.23
PICO3: J4.59, U7.23
PICO4: J5.59, U9.23
PICO5: J6.59, U11.23
PICO6: J7.59, U13.23
PICO7: J8.59, U15.23
PICO8: J9.59, U17.23
PICO9: J10.59, U19.23
PICO10: J11.59, U21.23
PICO11: J12.59, U23.23
PICO12: J13.59, U25.23
PICO13: J14.59, U27.23
PICO14: J15.59, U29.23
PICO15: J16.59, U31.23
POCI: J1.61, U1.22
POCI1: J2.61, U2.22
POCI2: J3.61, U5.22
POCI3: J4.61, U7.22
POCI4: J5.61, U9.22
POCI5: J6.61, U11.22
POCI6: J7.61, U13.22
POCI7: J8.61, U15.22
POCI8: J9.61, U17.22
POCI9: J10.61, U19.22
POCI10: J11.61, U21.22
POCI11: J12.61, U23.22
POCI12: J13.61, U25.22
POCI13: J14.61, U27.22
POCI14: J15.61, U29.22
POCI15: J16.61, U31.22
PWM0: J1.32, U1.37
PWM1: J1.47, U1.38
PWM2: J2.32, U2.37
PWM3: J2.47, U2.38
PWM4: J3.32, U5.37
PWM5: J3.47, U5.38
PWM6: J4.32, U7.37
PWM7: J4.47, U7.38
PWM8: J5.32, U9.37
PWM9: J5.47, U9.38
PWM10: J6.32, U11.37
PWM11: J6.47, U11.38
PWM12: J7.32, U13.37
PWM13: J7.47, U13.38
PWM14: J8.32, U15.37
PWM15: J8.47, U15.38
PWM16: J9.32, U17.37
PWM17: J9.47, U17.38
PWM18: J10.32, U19.37
PWM19: J10.47, U19.38
PWM20: J11.32, U21.37
PWM21: J11.47, U21.38
PWM22: J12.32, U23.37
PWM23: J12.47, U23.38
PWM24: J13.32, U25.37
PWM25: J13.47, U25.38
PWM26: J14.32, U27.37
PWM27: J14.47, U27.38
PWM28: J15.32, U29.37
PWM29: J15.47, U29.38
PWM30: J16.32, U31.37
PWM31: J16.47, U31.38
RX1: J1.19, U1.43
RX2: J2.19, U2.43
RX3: J3.19, U5.43
RX4: J4.19, U7.43
RX5: J5.19, U9.43
RX6: J6.19, U11.43
RX7: J7.19, U13.43
RX8: J8.19, U15.43
RX9: J9.19, U17.43
RX10: J10.19, U19.43
RX11: J11.19, U21.43
RX12: J12.19, U23.43
RX13: J13.19, U25.43
RX14: J14.19, U27.43
RX15: J15.19, U29.43
RX16: J16.19, U31.43
SCK: J1.57, U1.21
SCK1: J2.57, U2.21
SCK2: J3.57, U5.21
SCK3: J4.57, U7.21
SCK4: J5.57, U9.21
SCK5: J6.57, U11.21
SCK6: J7.57, U13.21
SCK7: J8.57, U15.21
SCK8: J9.57, U17.21
SCK9: J10.57, U19.21
SCK10: J11.57, U21.21
SCK11: J12.57, U23.21
SCK12: J13.57, U25.21
SCK13: J14.57, U27.21
SCK14: J15.57, U29.21
SCK15: J16.57, U31.21
SCL: J1.14, U1.29
SCL1: J1.53, U1.58
SCL2: J2.14, U2.29
SCL3: J2.53, U2.58
SCL4: J3.14, U5.29
SCL5: J3.53, U5.58
SCL6: J4.14, U7.29
SCL7: J4.53, U7.58
SCL8: J5.14, U9.29
SCL9: J5.53, U9.58
SCL10: J6.14, U11.29
SCL11: J6.53, U11.58
SCL12: J7.14, U13.29
SCL13: J7.53, U13.58
SCL14: J8.14, U15.29
SCL15: J8.53, U15.58
SCL16: J9.14, U17.29
SCL17: J9.53, U17.58
SCL18: J10.14, U19.29
SCL19: J10.53, U19.58
SCL20: J11.14, U21.29
SCL21: J11.53, U21.58
SCL22: J12.14, U23.29
SCL23: J12.53, U23.58
SCL24: J13.14, U25.29
SCL25: J13.53, U25.58
SCL26: J14.14, U27.29
SCL27: J14.53, U27.58
SCL28: J15.14, U29.29
SCL29: J15.53, U29.58
SCL30: J16.14, U31.29
SCL31: J16.53, U31.58
SDA: J1.12, U1.30
SDA1: J1.51, U1.59
SDA2: J2.12, U2.30
SDA3: J2.51, U2.59
SDA4: J3.12, U5.30
SDA5: J3.51, U5.59
SDA6: J4.12, U7.30
SDA7: J4.51, U7.59
SDA8: J5.12, U9.30
SDA9: J5.51, U9.59
SDA10: J6.12, U11.30
SDA11: J6.51, U11.59
SDA12: J7.12, U13.30
SDA13: J7.51, U13.59
SDA14: J8.12, U15.30
SDA15: J8.51, U15.59
SDA16: J9.12, U17.30
SDA17: J9.51, U17.59
SDA18: J10.12, U19.30
SDA19: J10.51, U19.59
SDA20: J11.12, U21.30
SDA21: J11.51, U21.59
SDA22: J12.12, U23.30
SDA23: J12.51, U23.59
SDA24: J13.12, U25.30
SDA25: J13.51, U25.59
SDA26: J14.12, U27.30
SDA27: J14.51, U27.59
SDA28: J15.12, U29.30
SDA29: J15.51, U29.59
SDA30: J16.12, U31.30
SDA31: J16.51, U31.59
STAT: R12.2, U1.50
STAT1: R8.2, U2.50
STAT2: R17.2, U5.50
STAT3: R24.2, U7.50
STAT4: R31.2, U9.50
STAT5: R38.2, U11.50
STAT6: R45.2, U13.50
STAT7: R52.2, U15.50
STAT8: R59.2, U17.50
STAT9: R66.2, U19.50
STAT10: R73.2, U21.50
STAT11: R80.2, U23.50
STAT12: R87.2, U25.50
STAT13: R94.2, U27.50
STAT14: R101.2, U29.50
STAT15: R108.2, U31.50
SWCLK: J1.21, U1.49
SWCLK1: J2.21, U2.49
SWCLK2: J3.21, U5.49
SWCLK3: J4.21, U7.49
SWCLK4: J5.21, U9.49
SWCLK5: J6.21, U11.49
SWCLK6: J7.21, U13.49
SWCLK7: J8.21, U15.49
SWCLK8: J9.21, U17.49
SWCLK9: J10.21, U19.49
SWCLK10: J11.21, U21.49
SWCLK11: J12.21, U23.49
SWCLK12: J13.21, U25.49
SWCLK13: J14.21, U27.49
SWCLK14: J15.21, U29.49
SWCLK15: J16.21, U31.49
SWDIO: J1.23, U1.46
SWDIO1: J2.23, U2.46
SWDIO2: J3.23, U5.46
SWDIO3: J4.23, U7.46
SWDIO4: J5.23, U9.46
SWDIO5: J6.23, U11.46
SWDIO6: J7.23, U13.46
SWDIO7: J8.23, U15.46
SWDIO8: J9.23, U17.46
SWDIO9: J10.23, U19.46
SWDIO10: J11.23, U21.46
SWDIO11: J12.23, U23.46
SWDIO12: J13.23, U25.46
SWDIO13: J14.23, U27.46
SWDIO14: J15.23, U29.46
SWDIO15: J16.23, U31.46
TX1: J1.17, U1.42
TX2: J2.17, U2.42
TX3: J3.17, U5.42
TX4: J4.17, U7.42
TX5: J5.17, U9.42
TX6: J6.17, U11.42
TX7: J7.17, U13.42
TX8: J8.17, U15.42
TX9: J9.17, U17.42
TX10: J10.17, U19.42
TX11: J11.17, U21.42
TX12: J12.17, U23.42
TX13: J13.17, U25.42
TX14: J14.17, U27.42
TX15: J15.17, U29.42
TX16: J16.17, U31.42

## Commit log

2020-12-07 V01 Update
    Added jumper for USB host config
    Updated crystal caps
2021-01-28 The 'ol pin switch-a-roo
    - Swapped D0/D1 with PWM0/1 - PWM pins weren't capable of PWM
    - Swapped BATT_VIN with STAT - BATT_VIN needs to be on an ADC pin
    - Moved PB13 to G10 - Based on testing VBUS needs to be broken out or pulled high for USB HS/FS to work correctly
    - Moved PB12 from jumper to G11 for USB Host ID to match with SAMD51 MM
    - Reorganized G0-G6 for better routing
2021-02-01 V10 design review changes
    Removed battery and 3.3V_EN connections to MicroMod
2021-02-02 Double-check changes
    - Added VDD range
    - Updated 0.1uF cap footprints from 0402 to 0402_TIGHT
2021-02-02 Added production panel
2021-02-03 Updated Panel
2021-03-29 Updated BOM
    Replaced 22 ohm resistors with 0 ohm
2021-04-12 Updated USB Load resistors
    Replaced 0 ohm resistors with 22 ohm
2022-09-27 Swap USART2 for USART1, connect USART2 to ground.
    Also renamed COPI/CIPO to POCI/PICO to match new naming conventions.
2022-09-27 Rerouted board, cleaned up schematic.
2022-09-27 Move some vias, replace STM32 with library part.
2022-09-29 Ready for v11 protos.
2022-09-30 Update for v20 pushing to reds.
2022-11-01 Updated from current libraries. Removed R4.
    Reset PUR unneeded per STM32 App Note AN4488.
2023-01-05 Centered title, re-enabled layers.
2023-01-05 Add v20 link to readme
